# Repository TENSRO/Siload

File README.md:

# Siload



**Low-cost retrofit weight sensing for existing silos.**



Siload is an open-source project for estimating the contents of a silo by measuring the strain in its existing support legs.



Instead of installing expensive load cells underneath the silo, small strain gauges are bonded directly to the structure. Siload measures these tiny deformations and converts them into an estimated silo weight.



The goal is simple:



> **Turn an existing silo into a smart weighing system without rebuilding it.**



---



## Why Siload?



Knowing how much material remains inside a silo is useful, but conventional weighing systems can be expensive and difficult to retrofit.



Traditional load-cell installations may require:



- lifting the silo;

- modifying its supports;

- installing multiple industrial load cells;

- mechanical engineering work;

- expensive instrumentation.



Siload takes a different approach.



```text

Traditional system



SILO

 │

 ▼

[ Load cell ]

 │

Foundation





Siload



SILO

 │

 │  ← strain gauges

 │

 │

Foundation

```



The silo stays where it is.



Siload measures how much its existing structure deforms under load.



---



## How it works



Steel stretches by an extremely small amount when it is loaded.



A strain gauge bonded to the silo leg changes resistance when this happens.



Siload measures that change using a Wheatstone bridge and a high-resolution ADC.



```text

Silo contents

     │

     ▼

 Mechanical load

     │

     ▼

 Silo leg strain

     │

     ▼

Strain gauges

     │

     ▼

Wheatstone bridge

     │

     ▼

  24-bit ADC

     │

     ▼

    ESP32

     │

     ▼

Filtering + calibration

     │

     ▼

Estimated silo weight

```



Measurements from multiple silo legs are combined to estimate the total load.



---



## Sensor concept



The intended configuration uses **four strain gauges per silo leg**.



```text

        SILO LEG



       Side A

        │

      [ V ]

        │

      [ H ]



        │

        │



       Side B

        │

      [ V ]

        │

      [ H ]



V = vertical strain gauge

H = transverse strain gauge

```



The gauges can be wired as a **full Wheatstone bridge**.



This configuration is intended to improve:



- temperature compensation;

- sensitivity;

- rejection of bending;

- rejection of uneven structural loading;

- long-term stability.



Each silo leg can be measured independently before the loads are combined in software.



---



## Prototype hardware



Siload uses **two compact, 100% through-hole 2-layer KiCad 10 carrier PCBs** built around the exact same **Seeed XIAO ESP32-S3 + stacked Wio-SX1262 (LoRa EU868)** MCU/radio module:



1. **Farm Hub (SILOAD REV A — 59 × 36 mm, [hardware/farm_hub/](hardware/farm_hub/)):** Bridges incoming LoRa telemetry packets from the silos to wired Ethernet via a **W5500 Lite** SPI-Ethernet module (J3/J4).

2. **Silo Unit / Load Cell PCB (SILOAD LOAD CELL REV A — 68 × 44 mm, [hardware/silo_unit/](hardware/silo_unit/)):** Reads **4 strain-gauge / load-cell bridges (J5–J8)** and **1 DS18B20 temperature sensor (J9)** using **1× horizontal Heemol HX711 24-bit ADC module (34 × 21 mm, J3/J4)** and **1× CD4052BE DIP-16 dual 4-channel differential analog multiplexer (U1)**, transmitting measurements over LoRa to the Farm Hub.



### Both PCBs Together (Farm Hub + Silo Unit)











### Individual Carrier PCBs



| **1. Farm Hub (SILOAD REV A — 59 × 36 mm)** | **2. Silo Unit / Load Cell PCB (SILOAD LOAD CELL REV A — 68 × 44 mm)** |

|---|---|

|  |  |

|  |  |

| **Role:** LoRa-to-Ethernet gateway (XIAO ESP32-S3 + Wio-SX1262 + W5500 Lite) | **Role:** 4-leg load-cell + temperature node (XIAO ESP32-S3 + Wio-SX1262 + HX711 + CD4052BE + DS18B20) |

| **Production Gerbers:** [SILOAD-FARM-HUB-REV-A-gerbers.zip](hardware/farm_hub/SILOAD-FARM-HUB-REV-A-gerbers.zip) ([gerbers/](hardware/farm_hub/gerbers/)) | **Production Gerbers:** [SILOAD-SILO-UNIT-REV-A-gerbers.zip](hardware/silo_unit/SILOAD-SILO-UNIT-REV-A-gerbers.zip) ([gerbers/](hardware/silo_unit/gerbers/)) |



### Why 1× HX711 + CD4052BE Multiplexer Instead of 4× HX711 + XIAO S3 Plus?



- **No XIAO ESP32-S3 Plus needed:** Both boards use the standard 14-pin **Seeed XIAO ESP32-S3 + Wio-SX1262** stack (J1/J2), avoiding underside SMD pad soldering (D11–D16).

- **Continuous bridge excitation + differential switching:** All 4 load cells (J5–J8) receive continuous E+/E- excitation from the HX711 (J4.6/J4.5) for thermal stability, while a single through-hole **CD4052BE / 74HC4052N DIP-16 multiplexer (U1, ~€0.25)** switches the selected sensor\'s (A+, A-) differential pair into the HX711 (J4.3/J4.4) on D0 (DT) and D6 (SCK).

- **Zero extra GPIOs required:** Channel select pins SEL_A (D8) and SEL_B (D10) reuse the SPI lines while LoRa NSS (D4) is HIGH (idle), and the DS18B20 temperature sensor sits on D7 with a 4.7 kΩ pull-up (R1).

- **Dual power options (USB-C or 5V DC header):** Both carrier boards feature dedicated 2-pin 2.54mm power headers (J5 on Farm Hub, J10 on Silo Unit) labeled 5V/GND, allowing direct 5V DC power from a DIN-rail supply, solar power board, or battery regulator without requiring a USB-C cable.



See [hardware/PINOUT.md](hardware/PINOUT.md) for the complete pinout and schematic/routing details.



---



## System architecture



```text

             SILO



       ┌──────┴──────┐

       │             │

    Leg 1          Leg 2

       │             │

   Strain          Strain

   bridge          bridge

       │             │

     ADC             ADC

       │             │

       └──────┬──────┘

              │

            ESP32

              │

       ┌──────┴───────┐

       │              │

      Wi-Fi          BLE

       │

       ▼

 Dashboard / API

```



Four-leg installations simply extend the same architecture with two additional measurement channels.



---



## Calibration



Accurate absolute weight measurement requires calibration because every silo is different.



Variables include:



- silo geometry;

- leg dimensions;

- steel properties;

- welds and brackets;

- foundation stiffness;

- gauge placement;

- load distribution;

- temperature.



Siload therefore focuses heavily on software-assisted calibration.



### Initial calibration



The simplest method is to record the sensor output at one or more known silo weights.



```text

ADC / strain

     │

     │           ● known load

     │        /

     │     /

     │  ●

     │/

     └──────────────────

             kg

```



More calibration points allow the system to compensate for structural nonlinearities.



### Shunt calibration



Future hardware may include electronically switched precision resistors for **shunt calibration**.



This allows the controller to inject a known electrical change into the Wheatstone bridge.



It can be used to verify the complete measurement chain:



```text

strain gauge

    ↓

wiring

    ↓

bridge

    ↓

ADC

    ↓

firmware

```



without physically loading the silo.



---



## Temperature compensation



Outdoor silos can experience large temperature changes.



Because the measured strains are extremely small, temperature effects cannot simply be ignored.



Siload aims to compensate for them using a combination of:



- full-bridge strain measurement;

- matched strain gauges;

- temperature sensing at each leg;

- software correction;

- long-term baseline tracking.



---



## Signal processing



Raw strain measurements are not directly converted into kilograms.



The firmware can process measurements using techniques such as:



```text

raw ADC

   ↓

outlier rejection

   ↓

low-pass filtering

   ↓

temperature compensation

   ↓

per-leg calibration

   ↓

load distribution correction

   ↓

total estimated weight

```



Slow-changing silo inventory is especially suitable for aggressive noise filtering because millisecond response times are unnecessary.



---



## Possible features



The long-term goal is more than simply displaying a number.



Siload could provide:



- real-time silo weight;

- estimated fill percentage;

- kilograms or tonnes remaining;

- consumption rate;

- refill detection;

- low-level alerts;

- historical inventory graphs;

- abnormal load-distribution detection;

- individual leg diagnostics;

- temperature compensation;

- automatic drift correction;

- sensor health monitoring;

- Wi-Fi connectivity;

- local web interface;

- MQTT / REST integration.



---



## Example dashboard



```text

Siload

────────────────────────



Feed Silo 01



████████████████░░░░  78%



        18,420 kg



Consumption

   612 kg / day



Estimated remaining

   30.1 days



Leg load

A   4,580 kg

B   4,710 kg

C   4,490 kg

D   4,640 kg



System

● Sensors OK

● Temperature compensated

● Connected

```



---



## Design goals



Siload is being designed around several principles.



**Low cost**



The sensing hardware should cost a fraction of a traditional industrial silo weighing retrofit.



**Retrofit-friendly**



Installation should require minimal changes to the existing silo.



**Non-invasive**



The silo should not need to be lifted simply to install weighing hardware.



**Smart**



Software should handle as much calibration, filtering, diagnostics and compensation as possible.



**Repairable**



The hardware and firmware should use accessible components and an open design.



**Scalable**



The same principle should eventually work with different silo sizes, geometries and numbers of support legs.



---



## Project status



> **Early development / experimental**



Siload is currently a research and prototype project.



Current focus:



- strain-gauge configuration;

- mechanical mounting;

- Wheatstone bridge design;

- low-noise acquisition;

- temperature compensation;

- calibration methods;

- long-term drift;

- ESP32 firmware;

- validation against known loads.



Absolute weighing accuracy has **not yet been established**.



---



## Roadmap



### Phase 1 — Bench testing



- [ ] Test BF350 / 350 Ω strain gauges

- [ ] Build full Wheatstone bridge

- [ ] Evaluate HX711 noise and stability

- [ ] Test temperature drift

- [ ] Develop ESP32 acquisition firmware



### Phase 2 — Structural prototype



- [ ] Instrument a steel test structure

- [ ] Compare strain against known loads

- [ ] Test bending rejection

- [ ] Develop multi-point calibration

- [ ] Evaluate long-term creep and drift



### Phase 3 — Silo prototype



- [ ] Install sensors on a real silo

- [ ] Instrument all support legs

- [ ] Compare against known filling events

- [ ] Implement temperature compensation

- [ ] Develop automatic health checks



### Phase 4 — Siload hardware



- [ ] Dedicated PCB

- [ ] Industrial enclosure

- [ ] Improved ADC architecture

- [ ] Protected sensor connections

- [ ] Shunt calibration

- [ ] Local dashboard

- [ ] MQTT / API support



---



## Important



Siload is an experimental measurement system.



It must **not** be used as a safety-critical structural monitoring system or as a certified/legal-for-trade weighing instrument.



Installing strain gauges on load-bearing structures must also be performed carefully to avoid damaging protective coatings or structural components.



---



## Contributing



Siload is in an early stage and experimentation is welcome.



Useful areas of research include:



- strain gauge layouts;

- bridge circuits;

- low-noise ADCs;

- temperature compensation;

- structural mechanics;

- calibration algorithms;

- enclosure design;

- ESP32 firmware;

- field testing.



Issues, test data and hardware experiments are welcome.



---



## Name



**Siload** combines:



**Silo + Load**



A simple description of what the project measures.



---



## License



License to be determined.



---



**Siload — weigh the silo, not rebuild it.**

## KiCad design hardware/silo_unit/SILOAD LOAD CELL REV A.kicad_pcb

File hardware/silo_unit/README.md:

# SILOAD LOAD CELL REV A — Silo Unit Carrier PCB (`68 × 44 mm`)

Zie [`ONTWERP.md`](ONTWERP.md) en [`../PINOUT.md`](../PINOUT.md) voor het volledige aansluitschema, de waarheidstabel van de `CD4052BE` multiplexer (`U1`) en de BOM (`BOM.csv`).

## Productie-Gerbers (JLCPCB / PCBWay / Eurocircuits)
- **Kant-en-klare ZIP voor upload:** [`SILOAD-SILO-UNIT-REV-A-gerbers.zip`](SILOAD-SILO-UNIT-REV-A-gerbers.zip)
- **Losse Gerber- en Excellon-boorbestanden:** [`gerbers/`](gerbers/) (`F.Cu`, `B.Cu`, `F.Mask`, `B.Mask`, `F.SilkS`, `B.SilkS`, `F.Paste`, `B.Paste`, `Edge.Cuts`, `PTH.drl`, `NPTH.drl`)

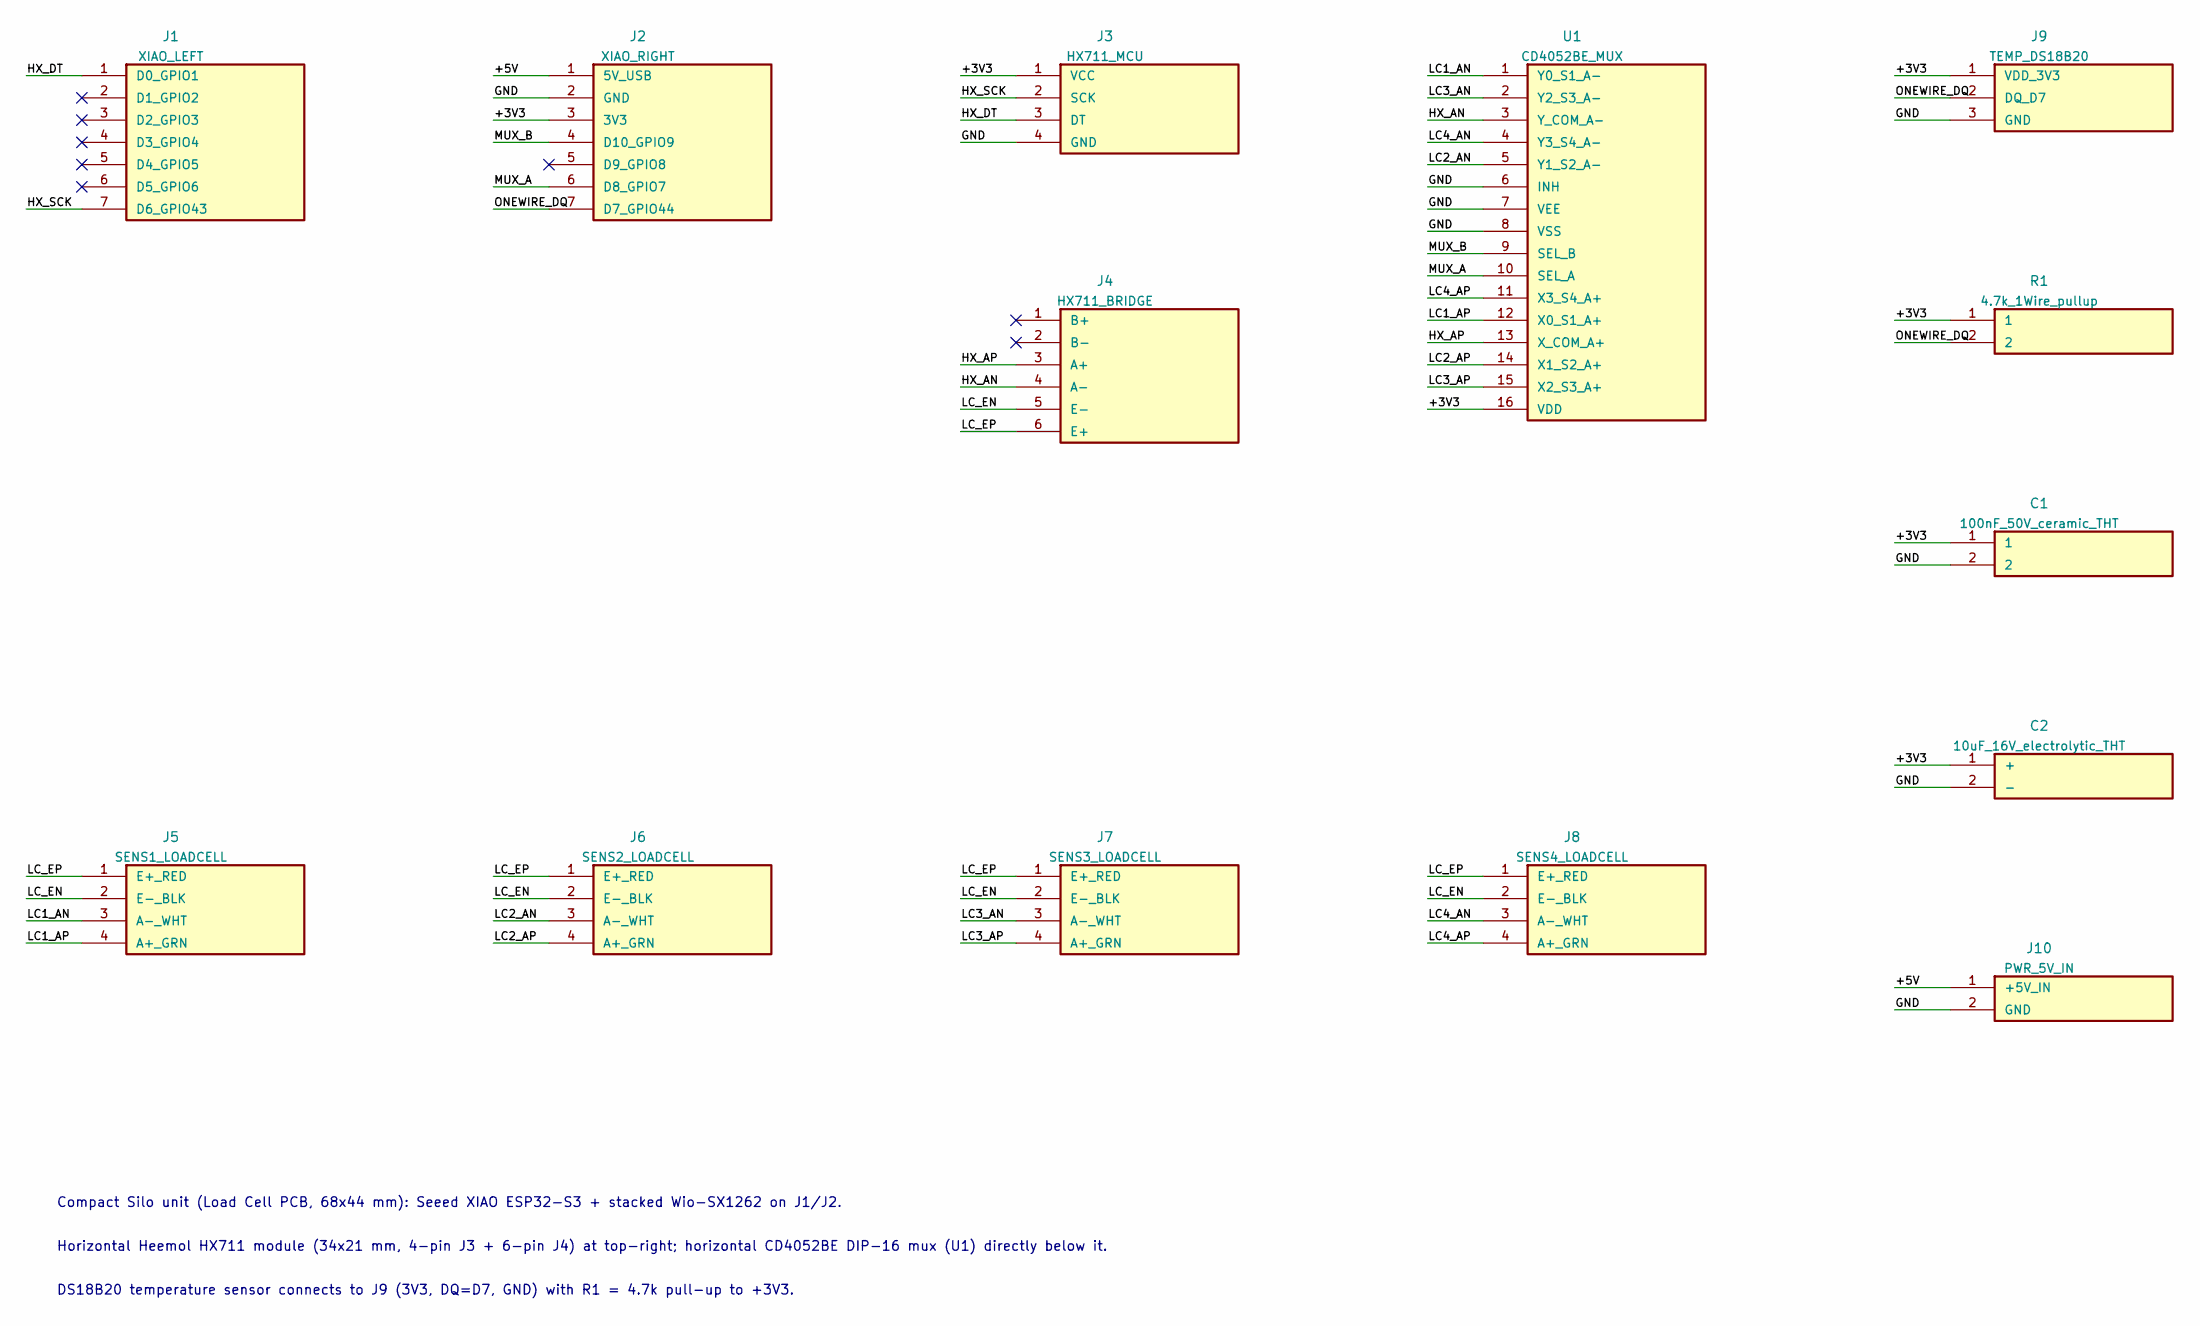
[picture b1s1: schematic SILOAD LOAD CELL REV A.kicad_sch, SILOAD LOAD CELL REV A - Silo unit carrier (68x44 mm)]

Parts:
C1: 100nF_50V_ceramic_THT; C_Disc_D5.0mm_W2.5mm_P2.50mm
C2: 10uF_16V_electrolytic_THT; CP_Radial_D5.0mm_P2.00mm
J1: XIAO_LEFT; PinSocket_1x07_P2.54mm_Vertical
J2: XIAO_RIGHT; PinSocket_1x07_P2.54mm_Vertical
J3: HX711_MCU; PinSocket_1x04_P2.54mm_Vertical
J4: HX711_BRIDGE; PinSocket_1x06_P2.54mm_Vertical
J5: SENS1_LOADCELL; PinSocket_1x04_P2.54mm_Vertical
J6: SENS2_LOADCELL; PinSocket_1x04_P2.54mm_Vertical
J7: SENS3_LOADCELL; PinSocket_1x04_P2.54mm_Vertical
J8: SENS4_LOADCELL; PinSocket_1x04_P2.54mm_Vertical
J9: TEMP_DS18B20; PinSocket_1x03_P2.54mm_Vertical
J10: PWR_5V_IN; PinSocket_1x02_P2.54mm_Vertical
R1: 4.7k_1Wire_pullup; R_Axial_DIN0207_L6.3mm_D2.5mm_P7.62mm_Horizontal
U1: CD4052BE_MUX; DIP-16_W7.62mm_Socket

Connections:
/+3V3: C1.1, C2.1 (+), J2.3 (3V3), J3.1 (VCC), J9.1 (VDD_3V3), R1.1, U1.16 (VDD)
/+5V: J2.1 (5V_USB), J10.1 (+5V_IN)
/GND: C1.2, C2.2 (-), J2.2 (GND), J3.4 (GND), J9.3 (GND), J10.2 (GND), U1.6 (INH), U1.7 (VEE), U1.8 (VSS)
/HX_AN: J4.4 (A-), U1.3 (Y_COM_A-)
/HX_AP: J4.3 (A+), U1.13 (X_COM_A+)
/HX_DT: J1.1 (D0_GPIO1), J3.3 (DT)
/HX_SCK: J1.7 (D6_GPIO43), J3.2 (SCK)
/LC1_AN: J5.3 (A-_WHT), U1.1 (Y0_S1_A-)
/LC1_AP: J5.4 (A+_GRN), U1.12 (X0_S1_A+)
/LC2_AN: J6.3 (A-_WHT), U1.5 (Y1_S2_A-)
/LC2_AP: J6.4 (A+_GRN), U1.14 (X1_S2_A+)
/LC3_AN: J7.3 (A-_WHT), U1.2 (Y2_S3_A-)
/LC3_AP: J7.4 (A+_GRN), U1.15 (X2_S3_A+)
/LC4_AN: J8.3 (A-_WHT), U1.4 (Y3_S4_A-)
/LC4_AP: J8.4 (A+_GRN), U1.11 (X3_S4_A+)
/LC_EN: J4.5 (E-), J5.2 (E-_BLK), J6.2 (E-_BLK), J7.2 (E-_BLK), J8.2 (E-_BLK)
/LC_EP: J4.6 (E+), J5.1 (E+_RED), J6.1 (E+_RED), J7.1 (E+_RED), J8.1 (E+_RED)
/MUX_A: J2.6 (D8_GPIO7), U1.10 (SEL_A)
/MUX_B: J2.4 (D10_GPIO9), U1.9 (SEL_B)
/ONEWIRE_DQ: J2.7 (D7_GPIO44), J9.2 (DQ_D7), R1.2

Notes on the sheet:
Compact Silo unit (Load Cell PCB, 68x44 mm): Seeed XIAO ESP32-S3 + stacked Wio-SX1262 on J1/J2.
Horizontal Heemol HX711 module (34x21 mm, 4-pin J3 + 6-pin J4) at top-right; horizontal CD4052BE DIP-16 mux (U1) directly below it.
DS18B20 temperature sensor connects to J9 (3V3, DQ=D7, GND) with R1 = 4.7k pull-up to +3V3.

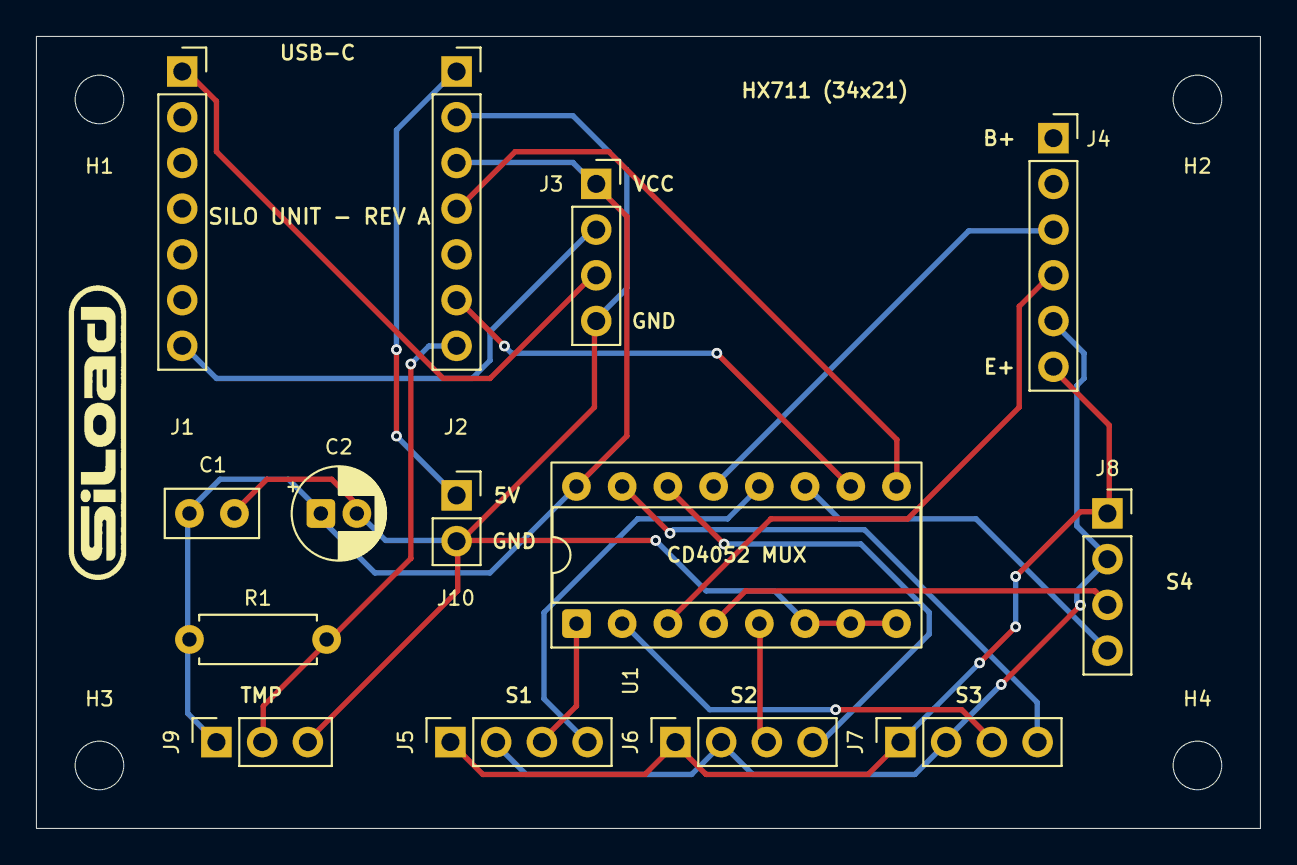
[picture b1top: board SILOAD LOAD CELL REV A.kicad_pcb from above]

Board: 2 copper layers, 68.0 x 44.0 mm, 19 parts (0 on the bottom side), 20 nets.

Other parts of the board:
H1, H2, H3, H4: M2.5; MountingHole_2.7mm_M2.5
LOGO1: SiLoad badge vertical

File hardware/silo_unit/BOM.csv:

Reference,Quantity,Description,Footprint
"J1,J2",2,Female header 1x7 2.54mm for XIAO ESP32-S3 + Wio-SX1262 stack,PinSocket_1x07_P2.54mm_Vertical
J3,1,"Female header 1x4 2.54mm for Heemol HX711 MCU side (VCC, SCK, DT, GND)",PinSocket_1x04_P2.54mm_Vertical
J4,1,"Female header 1x6 2.54mm for Heemol HX711 Bridge side (B+, B-, A+, A-, E-, E+)",PinSocket_1x06_P2.54mm_Vertical
U1,1,CD4052BE or 74HC4052N dual 4-channel analog multiplexer (DIP-16) + 16-pin DIP socket,DIP-16_W7.62mm_Socket
J5..J8,4,"4-pin 2.54mm header/socket for 4 load-cell sensors (E+, E-, A-, A+)",PinSocket_1x04_P2.54mm_Vertical
J9,1,"3-pin 2.54mm header/socket for DS18B20 temperature sensor (3V3, DQ, GND)",PinSocket_1x03_P2.54mm_Vertical
J10,1,"2-pin 2.54mm power header/socket (+5V, GND) for external 5V supply",PinSocket_1x02_P2.54mm_Vertical
R1,1,4.7k Ohm axial through-hole resistor (1-Wire pull-up to 3V3),R_Axial_DIN0207_L6.3mm_D2.5mm_P7.62mm_Horizontal
C1,1,100nF 50V ceramic through-hole decoupling capacitor,C_Disc_D5.0mm_W2.5mm_P2.50mm
C2,1,10uF 16V radial electrolytic bulk decoupling capacitor on 3V3,CP_Radial_D5.0mm_P2.00mm
H1..H4,4,"M2.5 mounting holes (2.7mm drill, screw head <=5mm)",MountingHole_2.7mm_M2.5

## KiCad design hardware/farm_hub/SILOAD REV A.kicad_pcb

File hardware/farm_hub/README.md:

# SILOAD REV A — Farm Hub Carrier PCB (`59 × 36 mm`)

Zie [`ONTWERP.md`](ONTWERP.md) en [`../PINOUT.md`](../PINOUT.md) voor het volledige aansluitschema en de BOM (`BOM.csv`).

## Productie-Gerbers (JLCPCB / PCBWay / Eurocircuits)
- **Kant-en-klare ZIP voor upload:** [`SILOAD-FARM-HUB-REV-A-gerbers.zip`](SILOAD-FARM-HUB-REV-A-gerbers.zip)
- **Losse Gerber- en Excellon-boorbestanden:** [`gerbers/`](gerbers/) (`F.Cu`, `B.Cu`, `F.Mask`, `B.Mask`, `F.SilkS`, `B.SilkS`, `F.Paste`, `B.Paste`, `Edge.Cuts`, `PTH.drl`, `NPTH.drl`)

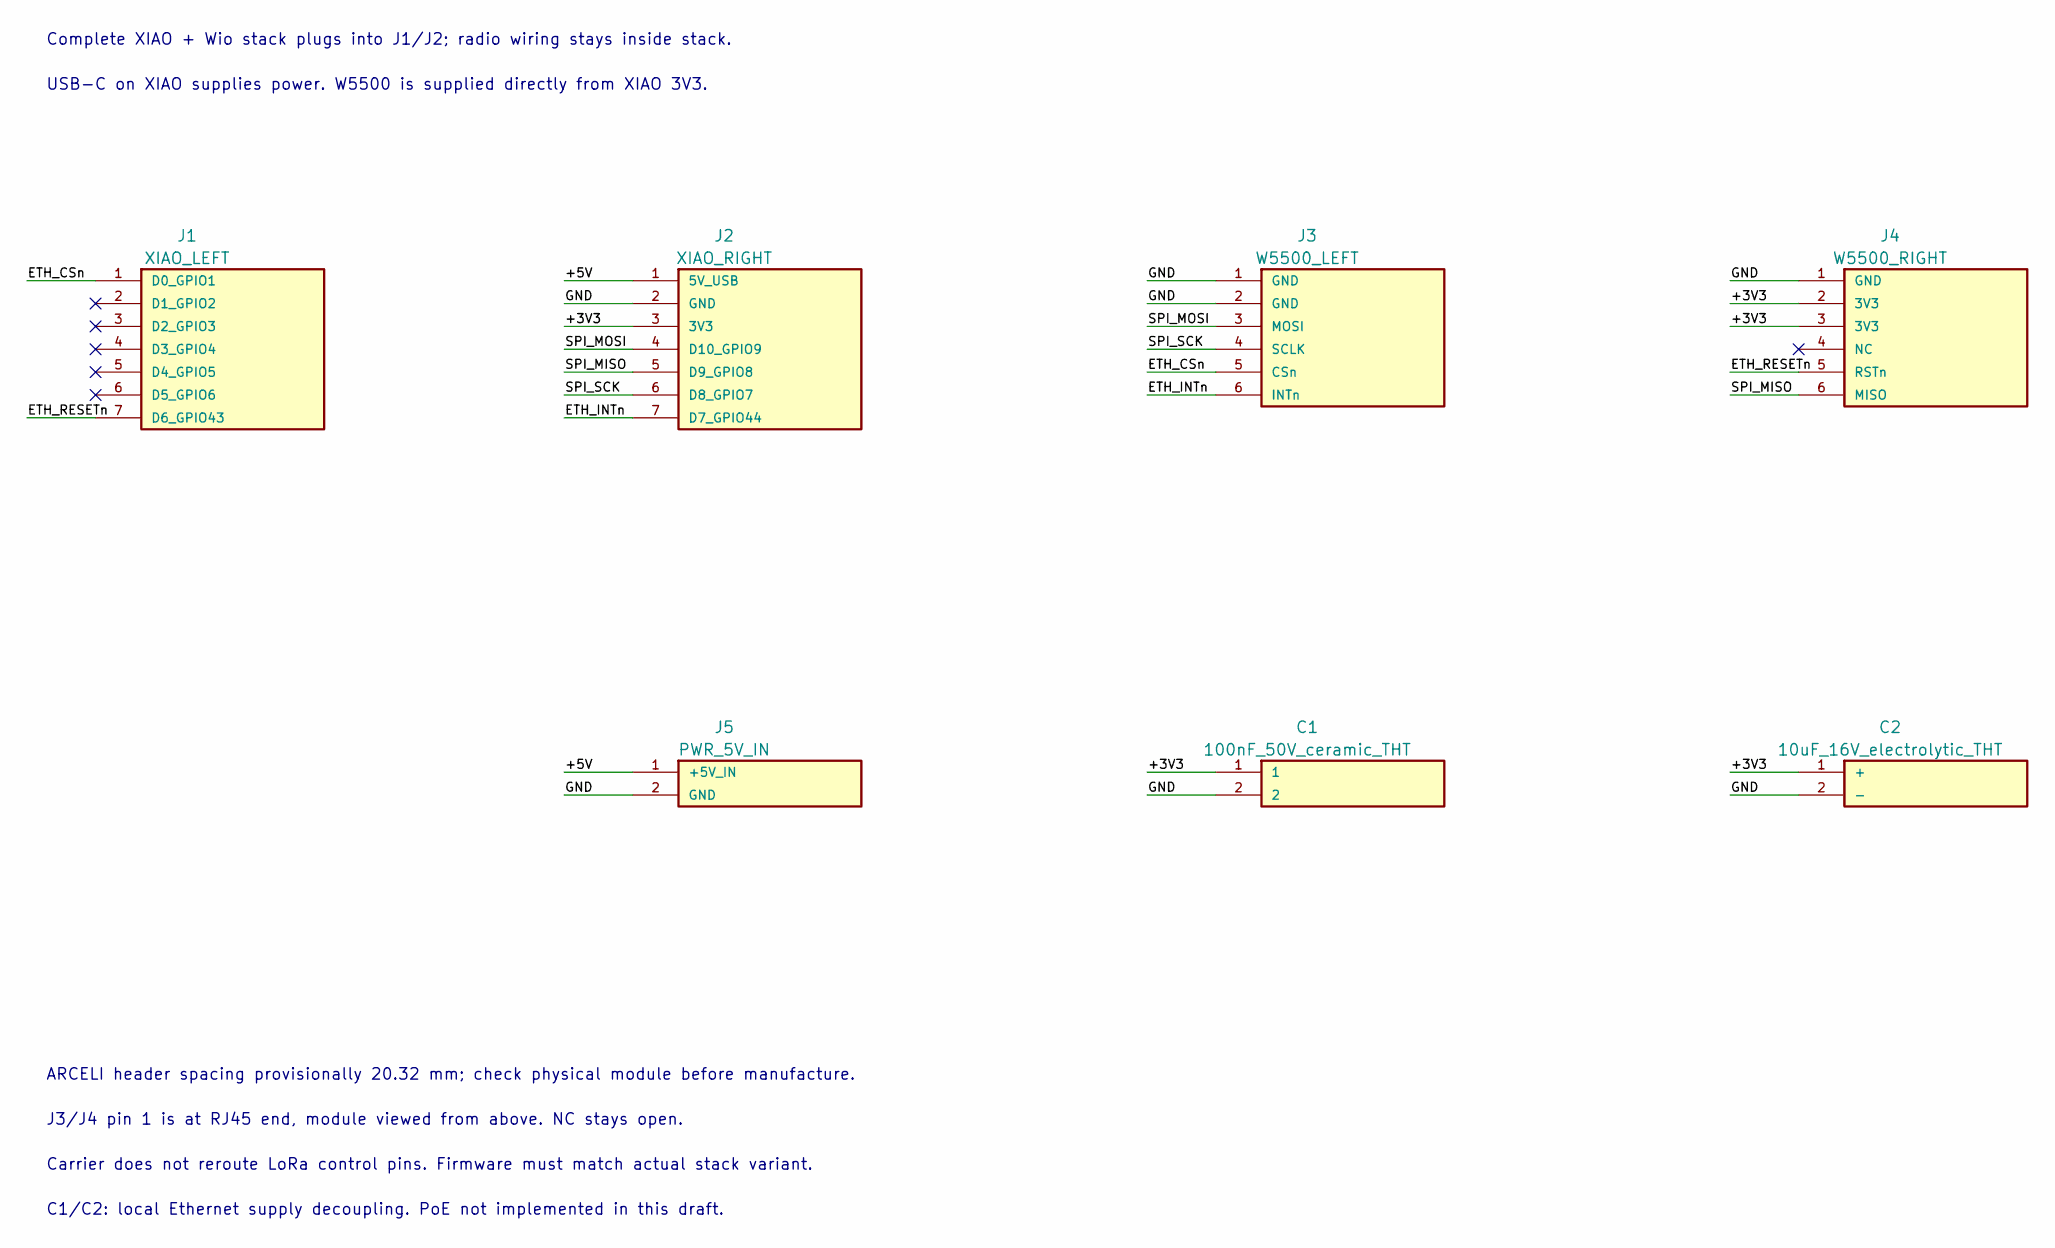
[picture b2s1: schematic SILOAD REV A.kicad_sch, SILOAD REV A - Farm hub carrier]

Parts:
C1: 100nF_50V_ceramic_THT; C_Disc_D5.0mm_W2.5mm_P2.50mm
C2: 10uF_16V_electrolytic_THT; CP_Radial_D5.0mm_P2.00mm
J1: XIAO_LEFT; PinSocket_1x07_P2.54mm_Vertical
J2: XIAO_RIGHT; PinSocket_1x07_P2.54mm_Vertical
J3: W5500_LEFT; PinSocket_1x06_P2.54mm_Vertical
J4: W5500_RIGHT; PinSocket_1x06_P2.54mm_Vertical
J5: PWR_5V_IN; PinSocket_1x02_P2.54mm_Vertical

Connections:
/+3V3: C1.1, C2.1 (+), J2.3 (3V3), J4.2 (3V3), J4.3 (3V3)
/+5V: J2.1 (5V_USB), J5.1 (+5V_IN)
/ETH_CSn: J1.1 (D0_GPIO1), J3.5 (CSn)
/ETH_INTn: J2.7 (D7_GPIO44), J3.6 (INTn)
/ETH_RESETn: J1.7 (D6_GPIO43), J4.5 (RSTn)
/GND: C1.2, C2.2 (-), J2.2 (GND), J3.1 (GND), J3.2 (GND), J4.1 (GND), J5.2 (GND)
/SPI_MISO: J2.5 (D9_GPIO8), J4.6 (MISO)
/SPI_MOSI: J2.4 (D10_GPIO9), J3.3 (MOSI)
/SPI_SCK: J2.6 (D8_GPIO7), J3.4 (SCLK)

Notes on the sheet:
Complete XIAO + Wio stack plugs into J1/J2; radio wiring stays inside stack.
USB-C on XIAO supplies power. W5500 is supplied directly from XIAO 3V3.
ARCELI header spacing provisionally 20.32 mm; check physical module before manufacture.
J3/J4 pin 1 is at RJ45 end, module viewed from above. NC stays open.
Carrier does not reroute LoRa control pins. Firmware must match actual stack variant.
C1/C2: local Ethernet supply decoupling. PoE not implemented in this draft.

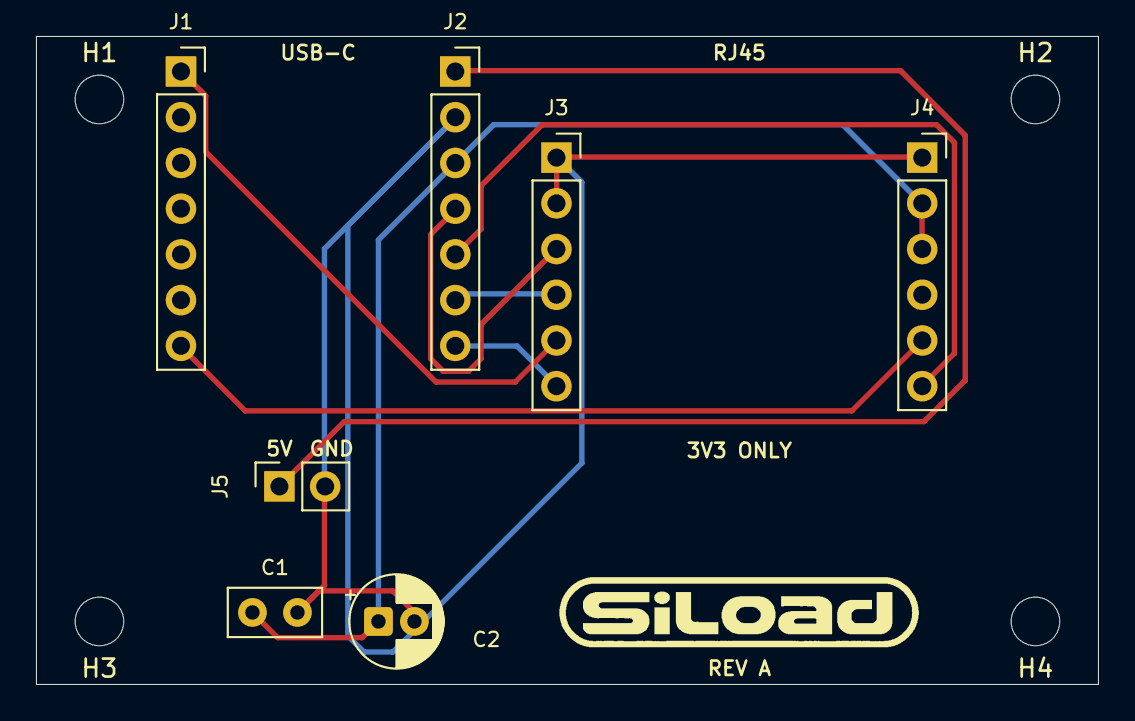
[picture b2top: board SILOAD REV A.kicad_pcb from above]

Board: 2 copper layers, 59.0 x 36.0 mm, 12 parts (0 on the bottom side), 9 nets.

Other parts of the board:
H1, H2, H3, H4: M2.5; MountingHole_2.7mm_M2.5
LOGO1: SiLoad badge 20mm; SiLoad_Badge_20mm

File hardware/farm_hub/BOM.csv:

Reference,Quantity,Description,Footprint
"J1,J2",2,Female header 1x7 2.54mm; height must clear Wio stack,PinSocket_1x07_P2.54mm_Vertical
"J3,J4",2,Female header 1x6 2.54mm; ARCELI spacing provisional,PinSocket_1x06_P2.54mm_Vertical
J5,1,"2-pin 2.54mm power header/pads (+5V, GND) for external 5V supply",PinSocket_1x02_P2.54mm_Vertical
C1,1,100nF 50V ceramic through-hole,Disc D5.0mm P2.50mm
C2,1,10uF 16V radial electrolytic; pin 1 is positive,Radial D5.0mm P2.00mm
Mounting hardware,4,"M2.5 screws, head diameter <=5mm; spacers to match enclosure",2.7mm mounting holes

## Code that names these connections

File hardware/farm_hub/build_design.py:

"""Generate the review draft. Run with the Python supplied with KiCad 10."""
from pathlib import Path
import uuid, json, csv
import pcbnew as p
from layout_config import BOARD_WIDTH,BOARD_HEIGHT,MOUNTING_HOLES,REFERENCE_POSITIONS,XIAO_HEADERS,ETH_HEADERS

ROOT = Path(__file__).resolve().parent
NAME = 'SILOAD REV A'
LIB = Path(r'C:\Program Files\KiCad\10.0\share\kicad\footprints')
uid = lambda: str(uuid.uuid4())
sheet = uid()
spec = [
 ('J1','XIAO_LEFT',XIAO_HEADERS[0],XIAO_HEADERS[1],7,['ETH_CSn',None,None,None,None,None,'ETH_RESETn'],['D0_GPIO1','D1_GPIO2','D2_GPIO3','D3_GPIO4','D4_GPIO5','D5_GPIO6','D6_GPIO43']),
 ('J2','XIAO_RIGHT',XIAO_HEADERS[0]+15.24,XIAO_HEADERS[1],7,[None,'GND','+3V3','SPI_MOSI','SPI_MISO','SPI_SCK','ETH_INTn'],['5V_USB','GND','3V3','D10_GPIO9','D9_GPIO8','D8_GPIO7','D7_GPIO44']),
 ('J3','W5500_LEFT',ETH_HEADERS[0],ETH_HEADERS[1],6,['GND','GND','SPI_MOSI','SPI_SCK','ETH_CSn','ETH_INTn'],['GND','GND','MOSI','SCLK','CSn','INTn']),
 ('J4','W5500_RIGHT',ETH_HEADERS[0]+20.32,ETH_HEADERS[1],6,['GND','+3V3','+3V3',None,'ETH_RESETn','SPI_MISO'],['GND','3V3','3V3','NC','RSTn','MISO']),
 ('C1','100nF_50V_ceramic_THT',62,82,2,['+3V3','GND'],['1','2']),
 ('C2','10uF_16V_electrolytic_THT',69,82.5,2,['+3V3','GND'],['+','-']),
]
board=p.BOARD()
board.SetCopperLayerCount(2)
board.GetDesignSettings().SetBoardThickness(p.FromMM(1.6))
nets={}
for name in sorted({n for s in spec for n in s[5] if n}):
 n=p.NETINFO_ITEM(board,name); board.Add(n); nets[name]=n

def pos(x,y): return p.VECTOR2I(p.FromMM(x),p.FromMM(y))
def line(x1,y1,x2,y2,layer=p.Edge_Cuts,width=.05):
 s=p.PCB_SHAPE(); s.SetShape(p.SHAPE_T_SEGMENT); s.SetStart(pos(x1,y1)); s.SetEnd(pos(x2,y2)); s.SetLayer(layer); s.SetWidth(p.FromMM(width)); board.Add(s)
def text(t,x,y,size=1,layer=p.F_SilkS):
 a=p.PCB_TEXT(board); a.SetText(t); a.SetPosition(pos(x,y)); a.SetTextSize(pos(size,size)); a.SetTextThickness(p.FromMM(.15)); a.SetLayer(layer); board.Add(a)

x1=50+BOARD_WIDTH;y1=50+BOARD_HEIGHT
for a,b,c,d in [(50,50,x1,50),(x1,50,x1,y1),(x1,y1,50,y1),(50,y1,50,50)]: line(a,b,c,d)
text(NAME,86,81.5,1.1)
text('Farm hub',86,84.2,.8)
text('DRAFT - CHECK MODULE FIT',77.5,88,.8,p.Dwgs_User)
text('USB-C',65.65,50.9,.8)
text('RJ45',89.05,50.9,.8)
text('3V3 ONLY',89.05,73,.8)
# Approximate module envelopes, deliberately on a documentation layer.
for x0,y0,x1,y1 in [(56.75,48.97,74.53,70.467),(76.55,48.98,101.55,77.48)]:
 for a,b,c,d in [(x0,y0,x1,y0),(x1,y0,x1,y1),(x1,y1,x0,y1),(x0,y1,x0,y0)]: line(a,b,c,d,p.Dwgs_User,.1)

defs=[]; instances=[]; wires=[]; labels=[]; ncs=[]
schem_positions=[(45.72,55.88),(105.41,55.88),(170.18,55.88),(234.95,55.88),(170.18,110.49),(234.95,110.49)]
footprints={}; ids={}
for idx,(ref,value,x,y,count,connections,pinnames) in enumerate(spec):
 identifier=uid(); ids[ref]=identifier
 if ref.startswith('J'):
  libname='Connector_PinSocket_2.54mm'
  fpname=f'PinSocket_1x0{count}_P2.54mm_Vertical'
 else:
  libname='Capacitor_THT'
  fpname='C_Disc_D5.0mm_W2.5mm_P2.50mm' if ref=='C1' else 'CP_Radial_D5.0mm_P2.00mm'
 fp=p.FootprintLoad(str(LIB/(libname+'.pretty')),fpname)
 fp.SetFPIDAsString(libname+':'+fpname)
 fp.SetReference(ref); fp.SetValue(value); fp.SetPosition(pos(x,y))
 fp.SetPath(p.KIID_PATH('/'+sheet+'/'+identifier))
 for pad in fp.Pads():
  net=connections[int(pad.GetNumber())-1]
  if net: pad.SetNet(nets[net])
 fp.Reference().SetTextSize(pos(.8,.8)); fp.Reference().SetTextThickness(p.FromMM(.12))
 fp.Value().SetVisible(False)
 board.Add(fp); footprints[ref]=fp
 sx,sy=schem_positions[idx]
 symbol_name=ref+'_socket' if ref.startswith('J') else ref+'_capacitor'
 pins=[]
 for k,pinname in enumerate(pinnames):
  py=-k*2.54
  pins.append(f'(pin passive line (at -10.16 {py} 0) (length 5.08) (name "{pinname}" (effects (font (size 1 1)))) (number "{k+1}" (effects (font (size 1 1)))))')
 defs.append(f'''(symbol "SILOAD:{symbol_name}"
 (pin_names (offset 1.016)) (in_bom yes) (on_board yes)
 (property "Reference" "{ref[0]}" (at 0 3.81 0) (effects (font (size 1.27 1.27))))
 (property "Value" "{value}" (at 0 6.35 0) (effects (font (size 1.27 1.27))))
 (symbol "{symbol_name}_0_1" (rectangle (start -5.08 1.27) (end 15.24 {-count*2.54+1.27}) (stroke (width .254) (type default)) (fill (type background))))
 (symbol "{symbol_name}_1_1" {''.join(pins)}))''')
 instances.append(f'''(symbol (lib_id "SILOAD:{symbol_name}") (at {sx} {sy} 0) (unit 1)
 (in_bom yes) (on_board yes) (dnp no) (uuid "{identifier}")
 (property "Reference" "{ref}" (at {sx} {sy-5} 0) (effects (font (size 1.27 1.27))))
 (property "Value" "{value}" (at {sx} {sy-2.5} 0) (effects (font (size 1.27 1.27))))
 (property "Footprint" "{libname}:{fpname}" (at {sx} {sy} 0) (effects (font (size 1 1)) hide))
 {''.join(f'(pin "{k+1}" (uuid "{uid()}"))' for k in range(count))}
 (instances (project "{NAME}" (path "/{sheet}" (reference "{ref}") (unit 1)))))''')
 for k,net in enumerate(connections):
  px=round(sx-10.16,4); py=round(sy+k*2.54,4); lx=round(px-7.62,4)
  if net:
   wires.append(f'(wire (pts (xy {lx} {py}) (xy {px} {py})) (stroke (width 0) (type default)) (uuid "{uid()}"))')
   labels.append(f'(label "{net}" (at {lx} {py} 0) (effects (font (size 1 1)) (justify left bottom)) (uuid "{uid()}"))')
  else:
   ncs.append(f'(no_connect (at {px} {py}) (uuid "{uid()}"))')

for ref,x,y in MOUNTING_HOLES:
 fp=p.FootprintLoad(str(LIB/'MountingHole.pretty'),'MountingHole_2.7mm_M2.5')
 fp.SetReference(ref); fp.SetValue('M2.5'); fp.SetPosition(pos(x,y)); fp.Value().SetVisible(False); board.Add(fp)
 fp.SetAttributes(fp.GetAttributes() | p.FP_BOARD_ONLY)

notes=[('Complete XIAO + Wio stack plugs into J1/J2; radio wiring stays inside stack.',30,30),
 ('USB-C on XIAO supplies power. W5500 is supplied directly from XIAO 3V3.',30,35),
 ('ARCELI header spacing provisionally 20.32 mm; check physical module before manufacture.',30,145),
 ('J3/J4 pin 1 is at RJ45 end, module viewed from above. NC stays open.',30,150),
 ('Carrier does not reroute LoRa control pins. Firmware must match actual stack variant.',30,155),
 ('C1/C2: local Ethernet supply decoupling. PoE not implemented in this draft.',30,160)]
note_text=''.join(f'(text "{t}" (at {x} {y} 0) (effects (font (size 1.27 1.27)) (justify left bottom)) (uuid "{uid()}"))' for t,x,y in notes)
sch=f'''(kicad_sch (version 20250114) (generator "eeschema") (uuid "{sheet}") (paper "A4")
 (title_block (title "SILOAD REV A - Farm hub carrier") (date "2026-10-27") (rev "A DRAFT") (comment 1 "CHECK MODULE FIT BEFORE FABRICATION"))
 (lib_symbols {''.join(defs)})
 {''.join(wires)} {''.join(labels)} {''.join(ncs)} {note_text} {''.join(instances)}
 (sheet_instances (path "/" (page "1"))))'''
(ROOT/(NAME+'.kicad_sch')).write_text(sch,encoding='utf-8')
(ROOT/'SILOAD.kicad_sym').write_text('(kicad_symbol_lib (version 20241209) (generator "kicad_symbol_editor") '+''.join(d.replace('"SILOAD:', '"') for d in defs)+')',encoding='utf-8')
(ROOT/'sym-lib-table').write_text('(sym_lib_table (version 7) (lib (name "SILOAD") (type "KiCad") (uri "${KIPRJMOD}/SILOAD.kicad_sym") (options "") (descr "SILOAD carrier connectors")))',encoding='utf-8')
for fp in board.GetFootprints():
 if fp.GetReference() in REFERENCE_POSITIONS:fp.Reference().SetPosition(pos(*REFERENCE_POSITIONS[fp.GetReference()]))
if (ROOT/'branding'/'SiLoad-logo.json').exists():
 from apply_logo import apply
 apply(board)
p.SaveBoard(str(ROOT/(NAME+'.kicad_pcb')),board)
(ROOT/(NAME+'.kicad_pro')).write_text(json.dumps({'meta':{'filename':NAME+'.kicad_pro','version':1},'board':{'design_settings':{'rules':{'min_clearance':.2,'min_track_width':.2,'min_hole_clearance':.25,'min_copper_edge_clearance':.3}}}},indent=2),encoding='utf-8')
with (ROOT/'BOM.csv').open('w',newline='',encoding='utf-8') as f:
 w=csv.writer(f); w.writerow(['Reference','Quantity','Description','Footprint'])
 w.writerow(['J1,J2',2,'Female header 1x7 2.54mm; height must clear Wio stack','PinSocket_1x07_P2.54mm_Vertical'])
 w.writerow(['J3,J4',2,'Female header 1x6 2.54mm; ARCELI spacing provisional','PinSocket_1x06_P2.54mm_Vertical'])
 w.writerow(['C1',1,'100nF 50V ceramic through-hole','Disc D5.0mm P2.50mm'])
 w.writerow(['C2',1,'10uF 16V radial electrolytic; pin 1 is positive','Radial D5.0mm P2.00mm'])
 w.writerow(['Mounting hardware',4,'M2.5 screws, head diameter <=5mm; spacers to match enclosure','2.7mm mounting holes'])
print('Created schematic, project, PCB placement draft and BOM in',ROOT)
